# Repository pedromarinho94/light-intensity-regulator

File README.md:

# Environment Light Intensity Regulator using:
    -PmodAls [SPI]
    -8x8 mini LED Backpack [I2C]
    -Misra-C
    -FLASH, SRAM, EEPROM & HT16k33 MemoryTest
    -Schematic and PCB design using EAGLE 9.2.2

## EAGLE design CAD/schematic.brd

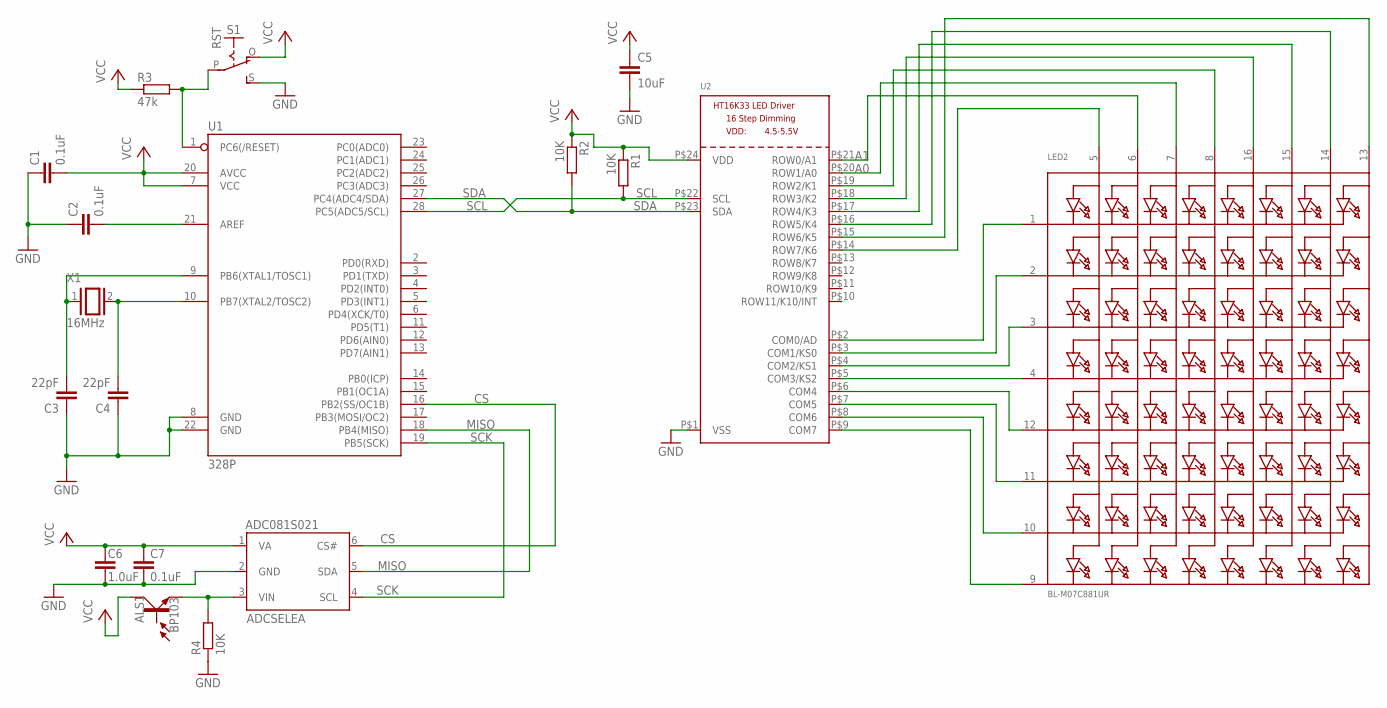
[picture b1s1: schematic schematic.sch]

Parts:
ADC081S021: ADCSELEA; SOT23
ALS1: BP103
C1, C2, C7: 0.1uF; 0402
C3, C4: 22pF; 0603
C5: 10uF; 0603
C6: 1.0uF; 0402
LED2: BL-M07C881UR; SEGMENT_BL-M07C881UR
R1, R2, R4: 10K; M0805
R3: 47k; M0805
S1: RST; EG1218
U1: 328P; MICROCONTROLLER_DIP28
U2: HT16K33_SOP24; SOP24_300MIL
X1: 16MHz; QS

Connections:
A0: LED2.7 (A3), U2.P$20 (ROW1/A0)
A1: LED2.6 (A2), U2.P$21 (ROW0/A1)
CS: ADC081S021.6 (CS#), U1.16 (PB2(SS/OC1B))
GND: ADC081S021.2 (GND), C1.1, C2.1, C3.1, C4.1, C5.2, C6.2, C7.2, R4.1, S1.S, U1.8 (GND), U1.22 (GND), U2.P$1 (VSS)
MISO: ADC081S021.5 (SDA), U1.18 (PB4(MISO))
unnamed: C4.2, U1.10 (PB7(XTAL2/TOSC2)), X1.2
unnamed: C3.2, U1.9 (PB6(XTAL1/TOSC1)), X1.1
unnamed: LED2.9 (K8), U2.P$9 (COM7)
unnamed: LED2.10 (K7), U2.P$8 (COM6)
unnamed: LED2.11 (K6), U2.P$7 (COM5)
unnamed: LED2.12 (K5), U2.P$6 (COM4)
unnamed: LED2.4 (K4), U2.P$5 (COM3/KS2)
unnamed: LED2.3 (K3), U2.P$4 (COM2/KS1)
unnamed: LED2.2 (K2), U2.P$3 (COM1/KS0)
unnamed: LED2.1 (K1), U2.P$2 (COM0/AD)
unnamed: LED2.8 (A4), U2.P$19 (ROW2/K1)
unnamed: LED2.16 (A5), U2.P$18 (ROW3/K2)
unnamed: LED2.15 (A6), U2.P$17 (ROW4/K3)
unnamed: ADC081S021.3 (VIN), ALS1.E, R4.2
unnamed: C2.2, U1.21 (AREF)
unnamed: LED2.5 (A1), U2.P$14 (ROW7/K6)
unnamed: R3.2, S1.P, U1.1 (PC6(/RESET))
SCK: ADC081S021.4 (SCL), U1.19 (PB5(SCK))
SCL: R1.2, U1.28 (PC5(ADC5/SCL)), U2.P$22 (SCL)
SDA: R2.2, U1.27 (PC4(ADC4/SDA)), U2.P$23 (SDA)
SEG_F: LED2.14 (A7), U2.P$16 (ROW5/K4)
SEG_G: LED2.13 (A8), U2.P$15 (ROW6/K5)
VCC: ADC081S021.1 (VA), ALS1.C, C1.2, C5.1, C6.1, C7.1, R1.1, R2.1, R3.1, S1.O, U1.7 (VCC), U1.20 (AVCC), U2.P$24 (VDD)

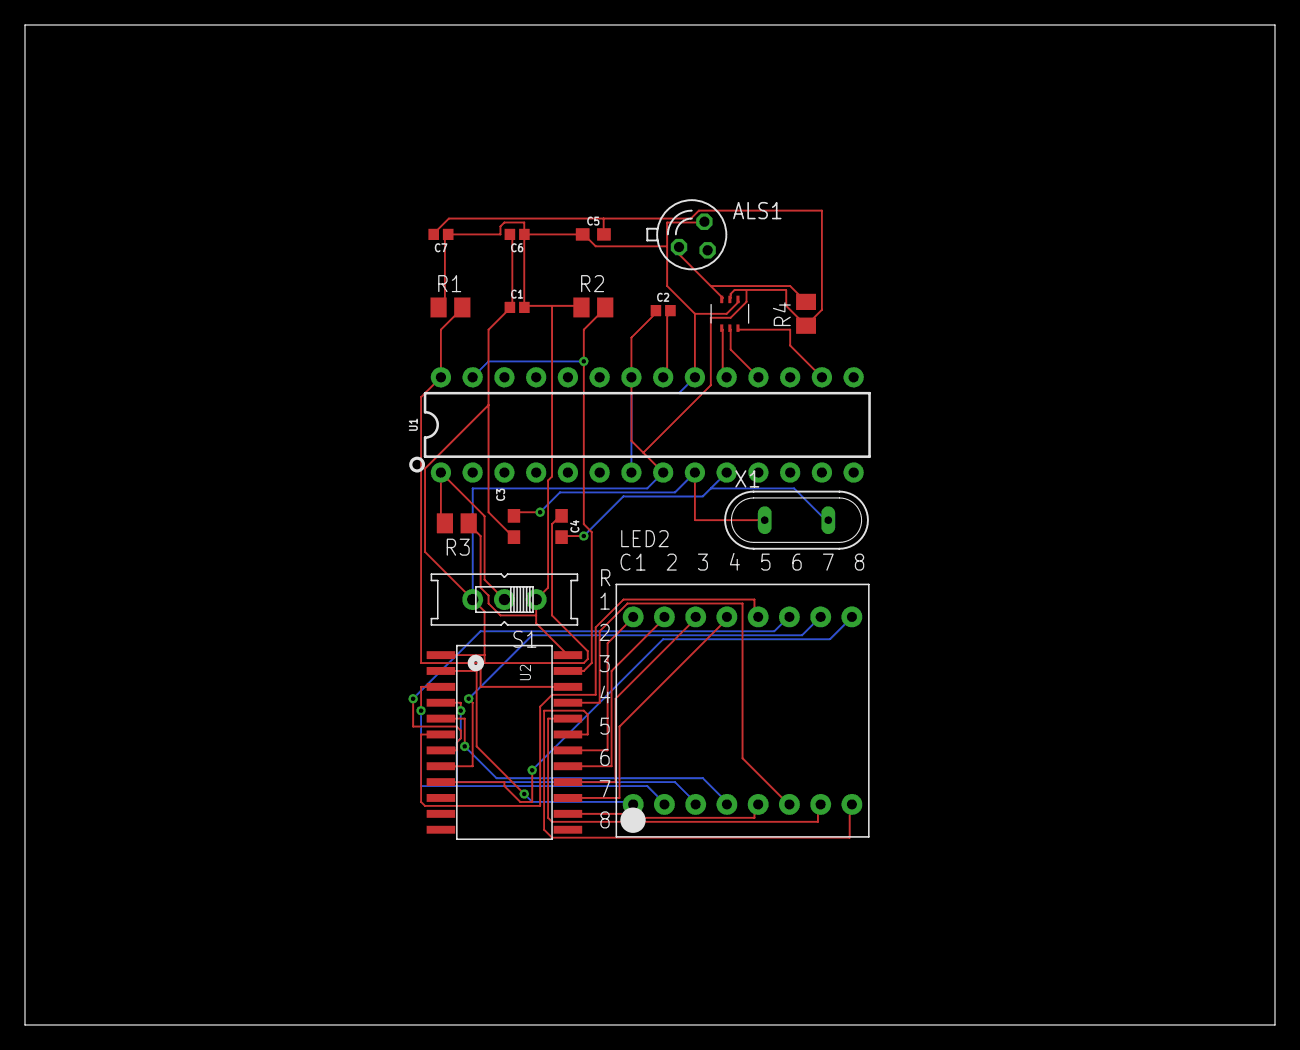
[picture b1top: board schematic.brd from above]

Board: 2 copper layers, 100.0 x 80.0 mm, 18 parts (0 on the bottom side), 28 nets.

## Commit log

2019-07-29 Add files via upload
    Project was originally on gitlab

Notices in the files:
parts and their libraries:
SparkFun-Capacitors: Licensing: Creative Commons ShareAlike 4.0 International - https://creativecommons.org/licenses/by-sa/4.0
